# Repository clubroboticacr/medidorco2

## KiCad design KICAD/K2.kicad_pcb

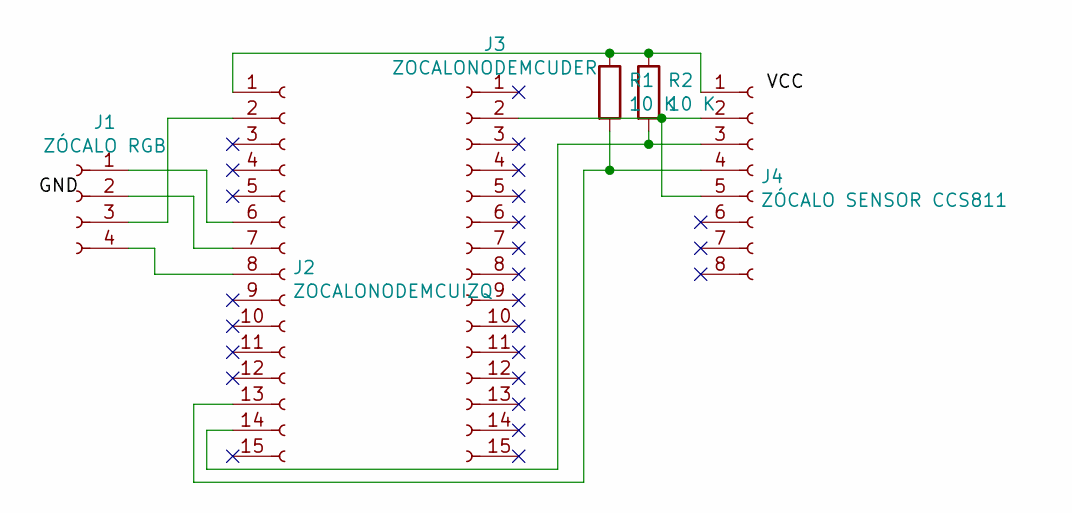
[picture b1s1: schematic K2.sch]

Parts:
J1: ZÓCALO RGB; PinSocket_1x04_P2.54mm_Vertical
J2: ZOCALONODEMCUIZQ; PinSocket_1x15_P2.54mm_Vertical
J3: ZOCALONODEMCUDER; PinSocket_1x15_P2.54mm_Vertical
J4: ZÓCALO SENSOR CCS811; PinSocket_1x08_P2.54mm_Vertical
R1, R2: 10 K; R_Axial_DIN0207_L6.3mm_D2.5mm_P7.62mm_Horizontal

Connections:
unnamed: J1.1, J2.6
unnamed: J1.2, J2.7
unnamed: J1.3, J2.2
unnamed: J1.4, J2.8
unnamed: J2.1, J4.1, R1.1, R2.1
unnamed: J2.13, J4.4, R1.2
unnamed: J2.14, J4.3, R2.2
unnamed: J3.2, J4.2, J4.5

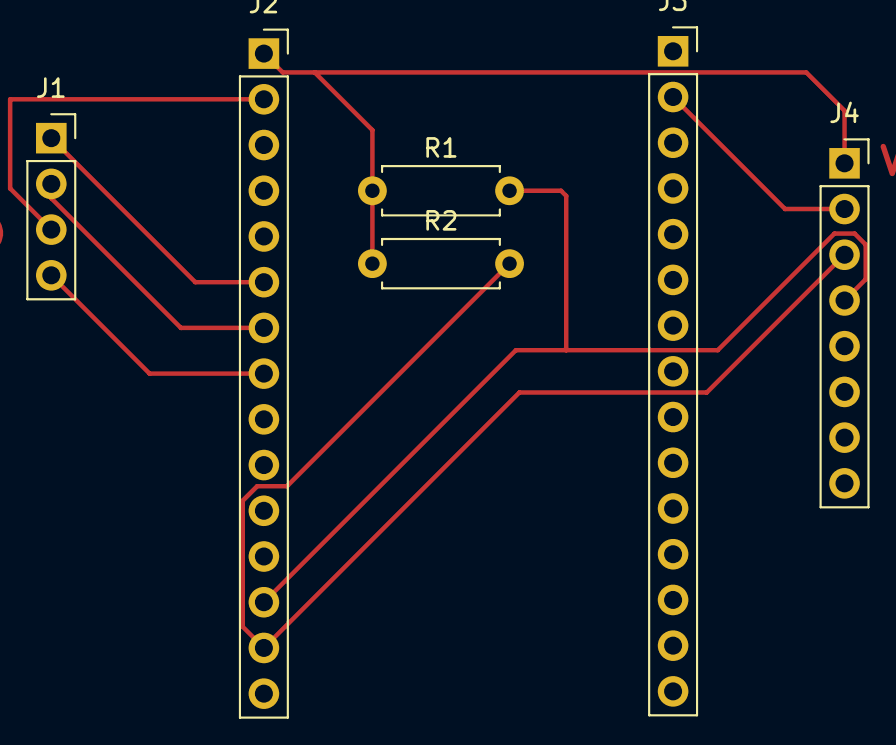
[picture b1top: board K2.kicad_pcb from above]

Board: 2 copper layers, 6 parts (0 on the bottom side), 8 nets.

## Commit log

2020-12-14 Empezando a crear el repo
2020-12-14 Este archivo debería estar en el servidor donde tenemos la base de datos
2020-12-14 Añadido proyecto KICAD
